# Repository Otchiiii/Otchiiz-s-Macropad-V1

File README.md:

# Otchiiz's Macropad V1

*An almost finished view of the Macropad.*

## 📖 Description
Very simple and basic 9 keys macropad.

*   **Firmware:** QMK CONFIGURATOR | QMK FIRMWARE

---

## ⚡ Electronics Design

This project utilizes a custom PCB designed in KiCad.

### Schematic

### PCB Layout

---

## ⚙️ Mechanical Design (The Case)

The enclosure was designed in Fusion360 to ensure a tight fit for the PCB and comfortable ergonomics.

### Case Assembly

*Exploded view or assembled view of the 3D printed case showing how the PCB fits inside.*

---

## 🛒 Bill of Materials (BOM)

| Part Name | Quantity | Description |
| :--- | :---: | ---: |
| **Microcontroller** | 1 | Seeed XIAO RP2040 | 
| **Switches** | 9 | Cherry MX Style Mechanical Switches | 
| **Keycaps** | 9 | DSA Profile Keycaps |
| **Screws** | 4 | M3 x 16mm Screws|
| **Filament** | - | PLA for Case | 

---

## 🚀 Getting Started

### Prerequisites
*   Soldering Iron & Solder
*   Specific Firmware Uploader (if needed)

### Assembly Instructions
1.  **Print the Case:** Use the STL files located in the `CAD` folder.
2.  **Solder the PCB:** Solder the microcontroller and switches to the PCB.
3.  **Firmware:** Plug in the device and copy the Firmware file to the root directory.
4.  **Final Assembly:** Insert the PCB into the case and secure with M3 screws.

---

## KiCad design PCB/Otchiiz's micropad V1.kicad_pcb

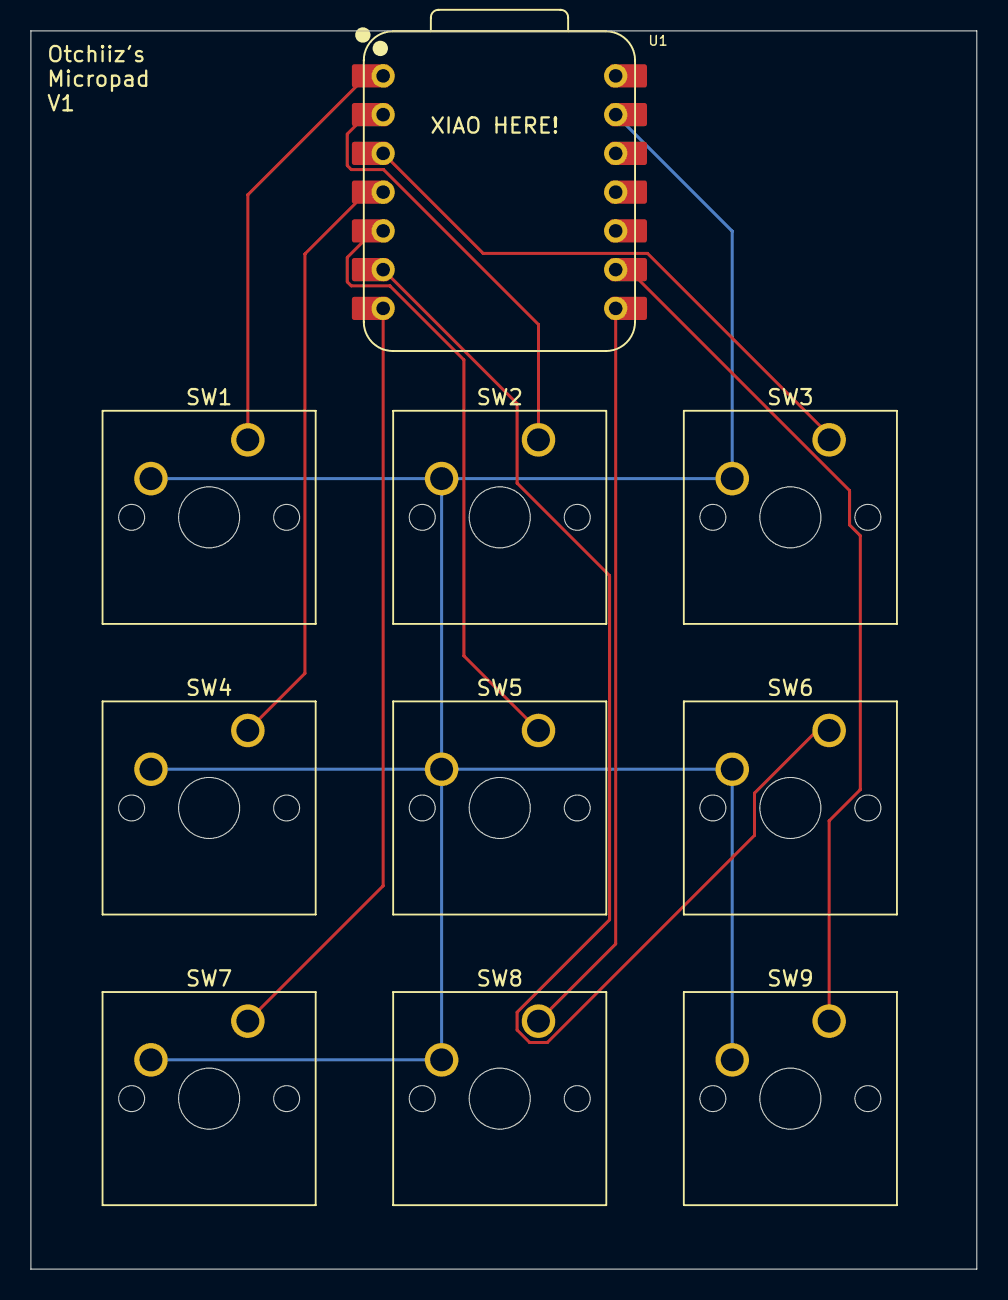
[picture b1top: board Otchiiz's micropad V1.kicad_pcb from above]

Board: 2 copper layers, 62.0 x 81.2 mm, 10 parts (0 on the bottom side), 10 nets.

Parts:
SW1, SW2, SW3, SW4, SW5, SW6, SW7, SW8, SW9: SW_Push; SW_Cherry_MX_1.00u_PCB
U1: XIAO-RP2040-DIP

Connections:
GND: SW1.2, SW2.2, SW3.2, SW4.2, SW5.2, SW6.2, SW7.2, SW8.2, SW9.2, U1.13 (GND)
unnamed: SW7.1, U1.7 (GPIO0/TX)
unnamed: SW8.1, U1.8 (GPIO1/RX)
unnamed: SW9.1, U1.9 (GPIO2/SCK)
unnamed: SW5.1, U1.5 (GPIO6/SDA)
unnamed: SW6.1, U1.6 (GPIO7/SCL)
unnamed: SW1.1, U1.1 (GPIO26/ADC0/A0)
unnamed: SW2.1, U1.2 (GPIO27/ADC1/A1)
unnamed: SW3.1, U1.3 (GPIO28/ADC2/A2)
unnamed: SW4.1, U1.4 (GPIO29/ADC3/A3)

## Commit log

2025-12-04 new file: CAD/Full.step new file: Firmware/9key_layout_2025-12-04.hex new file: Firmware/qmk_firmware-9key-layout_2025-12-04.zip new file: PCB/Otchiiz's micropad V1.kicad_pcb new file: PCB/Otchiiz's 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
2025-12-04 modified: README.md new file: images/case_assembly.png new file: images/overall_prototype.png new file: images/pcb_view.png new file: images/schematic.png
2025-12-04 modified: README.md
2025-12-04 modified: images/pcb_view.png
